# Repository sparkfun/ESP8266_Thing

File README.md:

SparkFun ESP8266 Thing
========================================

[*SparkFun ESP8266 Thing (WRL-13231)*](https://www.sparkfun.com/products/13231)

The [SparkFun ESP8266 Thing](https://www.sparkfun.com/products/13231) is essentially a breakout and development board for the ESP8266 WiFi SoC. Why the name? We lovingly call it the Thing due to it being the perfect foundation for your Internet of Things. Over the past year, the ESP8266 has been a growing star among IoT or WiFi-related projects. It’s an extremely cost-effective WiFi module, that – with a little extra effort – can be programmed just like any microcontroller. The only unfortunate part is: the ESP8266 has mostly only been available in a tiny, modular form, which, with limited I/O and a “unique” pin-out, can be difficult to build a project around. SparkFun’s new development board for the ESP8266 breaks out all of the module’s pins, and comes equipped with a LiPo charger, power supply, and all of the other supporting circuitry it requires.

The SparkFun ESP8266 Thing is a relatively simple board. The pins are broken out to two parallel, breadboard-compatible rows. USB and LiPo connectors at the top of the board provide power – controlled by the nearby ON/OFF switch. And LEDs towards the inside of the board indicate power, charge, and status of the IC. The ESP8266’s maximum voltage is 3.6V, so the Thing has an onboard 3.3V regulator to deliver a safe, consistent voltage to the IC. That means the ESP8266’s I/O pins also run at 3.3V, you’ll need to level shift any 5V signals running into the IC.

Repository Contents
-------------------

* **/Documentation** - Graphical datasheets (.pdf, .svg)
* **/Hardware** - Eagle design files (.brd, .sch)
* **/Production** - Production panel files (.brd)

Documentation
--------------
* **[Hookup Guide](https://learn.sparkfun.com/tutorials/esp8266-thing-hookup-guide)** - Exhaustive hookup guide for the ESP8266 Thing.
* **[SparkFun Fritzing repo](https://github.com/sparkfun/Fritzing_Parts)** - Fritzing diagrams for SparkFun products.
* **[SparkFun 3D Model repo](https://github.com/sparkfun/3D_Models)** - 3D models of SparkFun products. 

Product Versions
----------------
* [DEV-15258](https://www.sparkfun.com/products/15258)- The Thing in a starter kit.
* [DEV-13231](https://www.sparkfun.com/products/13231)- V1.0 release of the Thing.

License Information
-------------------

This product is _**open source**_! 

Please review the LICENSE.md file for license information. 

If you have any questions or concerns on licensing, please contact technical support on our [SparkFun forums](https://forum.sparkfun.com/viewforum.php?f=152).

Please use, reuse, and modify these files as you see fit. Please maintain attribution to SparkFun Electronics and release anything derivative under the same license.

Distributed as-is; no warranty is given.

- Your friends at SparkFun.

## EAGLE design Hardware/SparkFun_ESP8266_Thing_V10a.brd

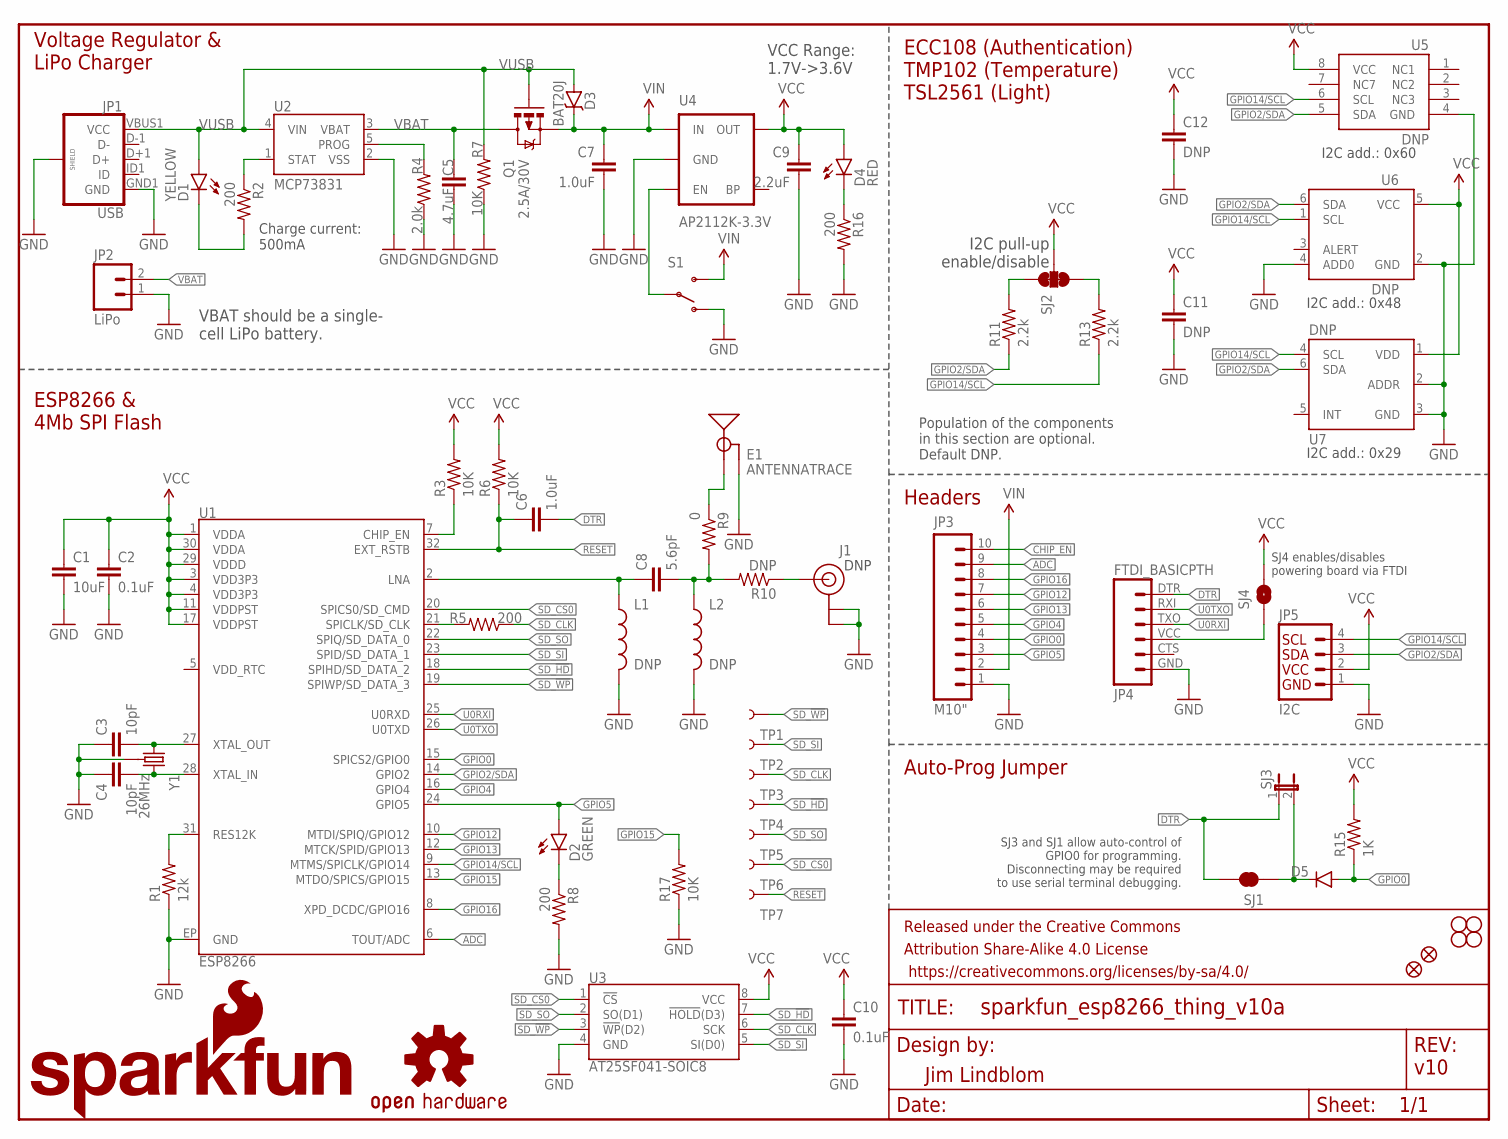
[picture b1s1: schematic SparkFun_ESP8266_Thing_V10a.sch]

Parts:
C1: 10uF; 0603-CAP
C2, C10: 0.1uF; 0603-CAP
C3, C4: 10pF; 0603-CAP
C5: 4.7uF; 0603-CAP
C6: 1.0uF; 0603-CAP
C7: 1.0uF; 0805
C8: 5.6pF; 0603-CAP
C9: 2.2uF; 0603-CAP
C11, C12: DNP; 0603-CAP
D1: YELLOW; LED-0603
D2: GREEN; LED-0603
D3: BAT20J; SOD-323
D4: RED; LED-0603
D5: DIODEBAS16; SOD-323
E1: ANTENNATRACE; TRACE_ANTENNA_2.4GHZ_25.7MM
FID1, FID2: FIDUCIAL1X2; FIDUCIAL-1X2
FRAME1: FRAME-LETTER; CREATIVE_COMMONS
J1: DNP; U.FL
JP1: USB; USB-B-MICRO-SMD_V03
JP2: LiPo; JST-2-PTH
JP3: M10"; 1X10
JP4: FTDI_BASICPTH; FTDI_BASIC
JP5: I2C; 1X04
L1, L2: DNP; 0603
LOGO1: SFE_LOGO_NAME.2_INCH; SFE_LOGO_NAME_.2
LOGO3: SFE_LOGO_FLAME.1_INCH; SFE_LOGO_FLAME_.1
LOGO4: OSHW-LOGOS; OSHW-LOGO-S
Q1: 2.5A/30V; SOT23-3
R1: 12k; 0603-RES
R2, R5, R8, R16: 200; 0603-RES
R3, R6, R7, R17: 10K; 0603-RES
R4: 2.0k; 0603-RES
R9: 0; 0603
R10: DNP; 0603-RES
R11, R13: 2.2k; 0603-RES
R15: 1K; 0603-RES
S1: SWITCH-SPDT-SMD-A; SWITCH-SPST-SMD-A
SJ1: JUMPER-PAD-2-NC_BY_TRACE; PAD-JUMPER-2-NC_BY_TRACE_YES_SILK
SJ2: JUMPER-PAD-3-NC_BY_TRACE; PAD-JUMPER-3-3OF3_NC_BY_TRACE_YES_SILK_FULL_BOX
SJ3: JUMPER-PTH-2-NC; PTH-JUMPER-NC_BOTTOM_NO_SILK
SJ4: JUMPER-PAD-2-NOYES_SILK; PAD-JUMPER-2-NO_YES_SILK
STANDOFF1, STANDOFF2, STANDOFF3, STANDOFF4: STAND-OFF
TP1, TP2, TP3, TP4, TP5, TP6, TP7: TEST-POINT3X5; PAD.03X.05
U1: ESP8266; QFN32
U2: MCP73831; SOT23-5
U3: AT25SF041-SOIC8; SO08
U4: AP2112K-3.3V; SOT23-5
U5: DNP; UDFN8
U6: DNP; SOT563-2
U7: DNP; FN-6
Y1: 26MHz; CRYSTAL-SMD-3.2X2.5

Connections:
ADC: JP3.9, U1.6 (TOUT/ADC)
ANT: J1.P$3 (SIGNAL), R10.1
CHIP_EN: JP3.10, R3.1, U1.7 (CHIP_EN)
DTR: C6.2, JP4.DTR (1), SJ1.2, SJ3.1
FTDI_VCC: JP4.VCC (4), SJ4.1
GND: C1.2, C2.2, C3.1, C4.1, C5.2, C7.2, C9.2, C10.2, C11.2, C12.2, E1.GND, E1.GND2 (GND), J1.P$1 (GND), J1.P$2 (GND), JP1.GND1 (GND), JP1.SHIELD1 (SHIELD), JP1.SHIELD2 (SHIELD), JP1.SHIELD3 (SHIELD), JP2.1, JP3.1, JP4.GND (6), JP5.1, L1.2, L2.2, R1.1, R4.1, R7.1, R8.2, R16.2, R17.1, S1.1 (O), U1.EP (GND), U2.2 (VSS), U3.4 (GND), U4.2 (GND), U5.4 (GND), U6.2 (GND), U6.4 (ADD0), U7.2 (ADDR), U7.3 (GND), Y1.2 (GND), Y1.4 (GND)
GPIO0: D5.A, JP3.4, R15.1, U1.15 (SPICS2/GPIO0)
GPIO2/SDA: JP5.3, R11.1, U1.14 (GPIO2), U5.5 (SDA), U6.6 (SDA), U7.6 (SDA)
GPIO4: JP3.5, U1.16 (GPIO4)
GPIO5: D2.A, JP3.3, U1.24 (GPIO5)
GPIO12: JP3.7, U1.10 (MTDI/SPIQ/GPIO12)
GPIO13: JP3.6, U1.12 (MTCK/SPID/GPIO13)
GPIO14/SCL: JP5.4, R13.1, U1.9 (MTMS/SPICLK/GPIO14), U5.6 (SCL), U6.1 (SCL), U7.4 (SCL)
GPIO15: R17.2, U1.13 (MTDO/SPICS/GPIO15)
GPIO16: JP3.8, U1.8 (XPD_DCDC/GPIO16)
LNA: C8.1, L1.1, U1.2 (LNA)
unnamed: R1.2, U1.31 (RES12K)
unnamed: C4.2, U1.28 (XTAL_IN), Y1.3 (2)
unnamed: C3.2, U1.27 (XTAL_OUT), Y1.1
unnamed: D4.C, R16.1
unnamed: C8.2, L2.1, R9.2, R10.2
unnamed: R5.2, U1.21 (SPICLK/SD_CLK)
unnamed: D5.C, SJ1.1, SJ3.2
unnamed: R11.2, SJ2.1
unnamed: R13.2, SJ2.3
unnamed: S1.2, U4.3 (EN)
unnamed: R4.2, U2.5 (PROG)
unnamed: D2.C, R8.1
unnamed: D1.C, R2.2
unnamed: R2.1, U2.1 (STAT)
RESET: C6.1, R6.1, TP7.P$1, U1.32 (EXT_RSTB)
SD_!HD!: TP4.P$1, U1.18 (SPIHD/SD_DATA_2), U3.7 (!HOLD!(D3))
SD_!WP!: TP1.P$1, U1.19 (SPIWP/SD_DATA_3), U3.3 (!WP!(D2))
SD_CLK: R5.1, TP3.P$1, U3.6 (SCK)
SD_CS0: TP6.P$1, U1.20 (SPICS0/SD_CMD), U3.1 (!CS!)
SD_SI: TP2.P$1, U1.23 (SPID/SD_DATA_1), U3.5 (SI(D0))
SD_SO: TP5.P$1, U1.22 (SPIQ/SD_DATA_0), U3.2 (SO(D1))
TRACE_ANT: E1.ANT (SIGNAL), R9.1
U0RXI: JP4.TXO (3), U1.25 (U0RXD)
U0TXO: JP4.RXI (2), U1.26 (U0TXD)
VBAT: C5.1, JP2.2, Q1.3 (D), U2.3 (VBAT)
VCC: C1.1, C2.1, C9.1, C10.1, C11.1, C12.1, D4.A, JP5.2, R3.2, R6.2, R15.2, SJ2.2, SJ4.2, U1.1 (VDDA), U1.3 (VDD3P3), U1.4 (VDD3P3), U1.11 (VDDPST), U1.17 (VDDPST), U1.29 (VDDD), U1.30 (VDDA), U3.8 (VCC), U4.5 (OUT), U5.8 (VCC), U6.5 (VCC), U7.1 (VDD)
VIN: C7.1, D3.C, JP3.2, Q1.2 (S), S1.3 (S), U4.1 (IN)
VUSB: D1.A, D3.A, JP1.VBUS1 (VCC), Q1.1 (G), R7.2, U2.4 (VIN)

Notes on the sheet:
Jim Lindblom
ECC108 (Authentication) TMP102 (Temperature) TSL2561 (Light)
Voltage Regulator & LiPo Charger
ESP8266 & 4Mb SPI Flash
Headers
Auto-Prog Jumper
v10
VCC Range: 1.7V->3.6V
VBAT should be a single- cell LiPo battery.
I2C pull-up enable/disable
SJ4 enables/disables powering board via FTDI
SJ3 and SJ1 allow auto-control of GPIO0 for programming. Disconnecting may be required to use serial terminal debugging.
I2C add.: 0x48
I2C add.: 0x60
I2C add.: 0x29
Population of the components in this section are optional. Default DNP.
Charge current: 500mA
DNP

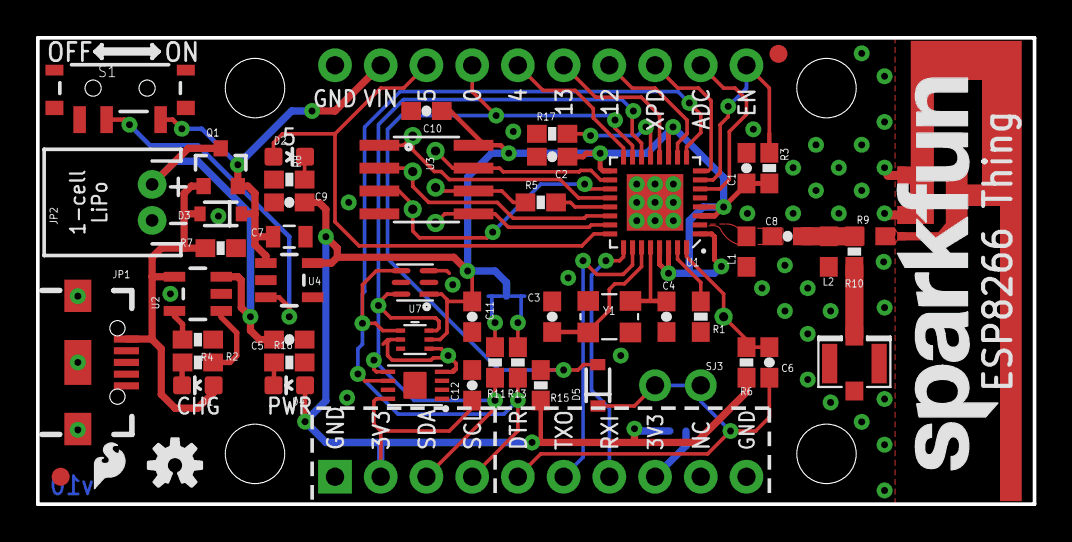
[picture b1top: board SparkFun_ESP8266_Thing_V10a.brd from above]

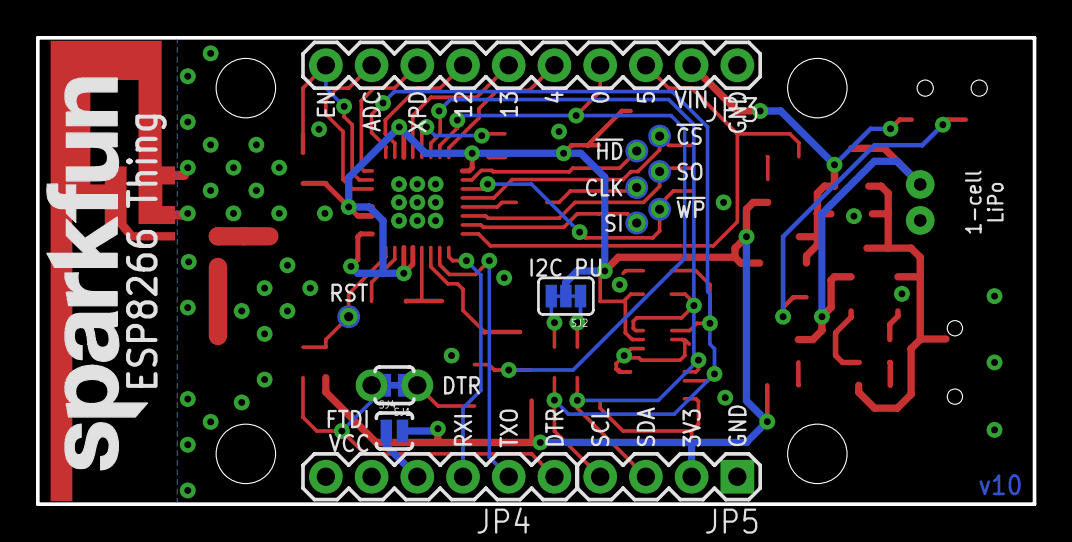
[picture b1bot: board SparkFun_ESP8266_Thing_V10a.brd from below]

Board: 2 copper layers, 55.4 x 25.9 mm, 73 parts (14 on the bottom side), 44 nets.

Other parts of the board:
LOGO5: SFE_LOGO_NAME.2_INCH; SFE_LOGO_NAME_.2

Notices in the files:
parts and their libraries:
SparkFun-Capacitors: Licensing: Creative Commons ShareAlike 4.0 International - https://creativecommons.org/licenses/by-sa/4.0
SparkFun-Aesthetics: Released under the Creative Commons Attribution Share-Alike 4.0 License
SparkFun-Aesthetics: https://creativecommons.org/licenses/by-sa/4.0
